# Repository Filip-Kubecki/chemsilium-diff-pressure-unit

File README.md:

# Pressure Measurement Unit - Chemsilium

A differential pressure acquisition system developed for the **Chemsilium Science Club**. This project integrates a **BMP280** (for ambient barometric pressure as calibration point) and dual *MPXM2202GS/AS* setup for differential pressure measurement.

## Repository Structure

The project is organized into four main branches to ensure maintainability:

* **`/hardware`**: Contains **KiCad** PCB and electronic design files.
  <!-- * `sch/`: Schematic diagrams. -->
  <!-- * `pcb/`: Board layout and routing. -->
  <!-- * `fabrication/`: Production-ready Gerbers, BOM (Bill of Materials), and CPL files. -->
* **`/firmware`**: Source code for the **Arduino/C++** embedded system.
  * Handles I2C communication with sensors.
  * Manages data packet formatting for serial transmission (using UART).
* **`/software`**: Desktop application scripts for data visualization and logging.
  * Real-time graphing of pressure trends.
  * CSV logging for post-experimental analysis.
* **`/docs`**: Technical documentation, including user manual with setup, maintenance and use explanations.

---

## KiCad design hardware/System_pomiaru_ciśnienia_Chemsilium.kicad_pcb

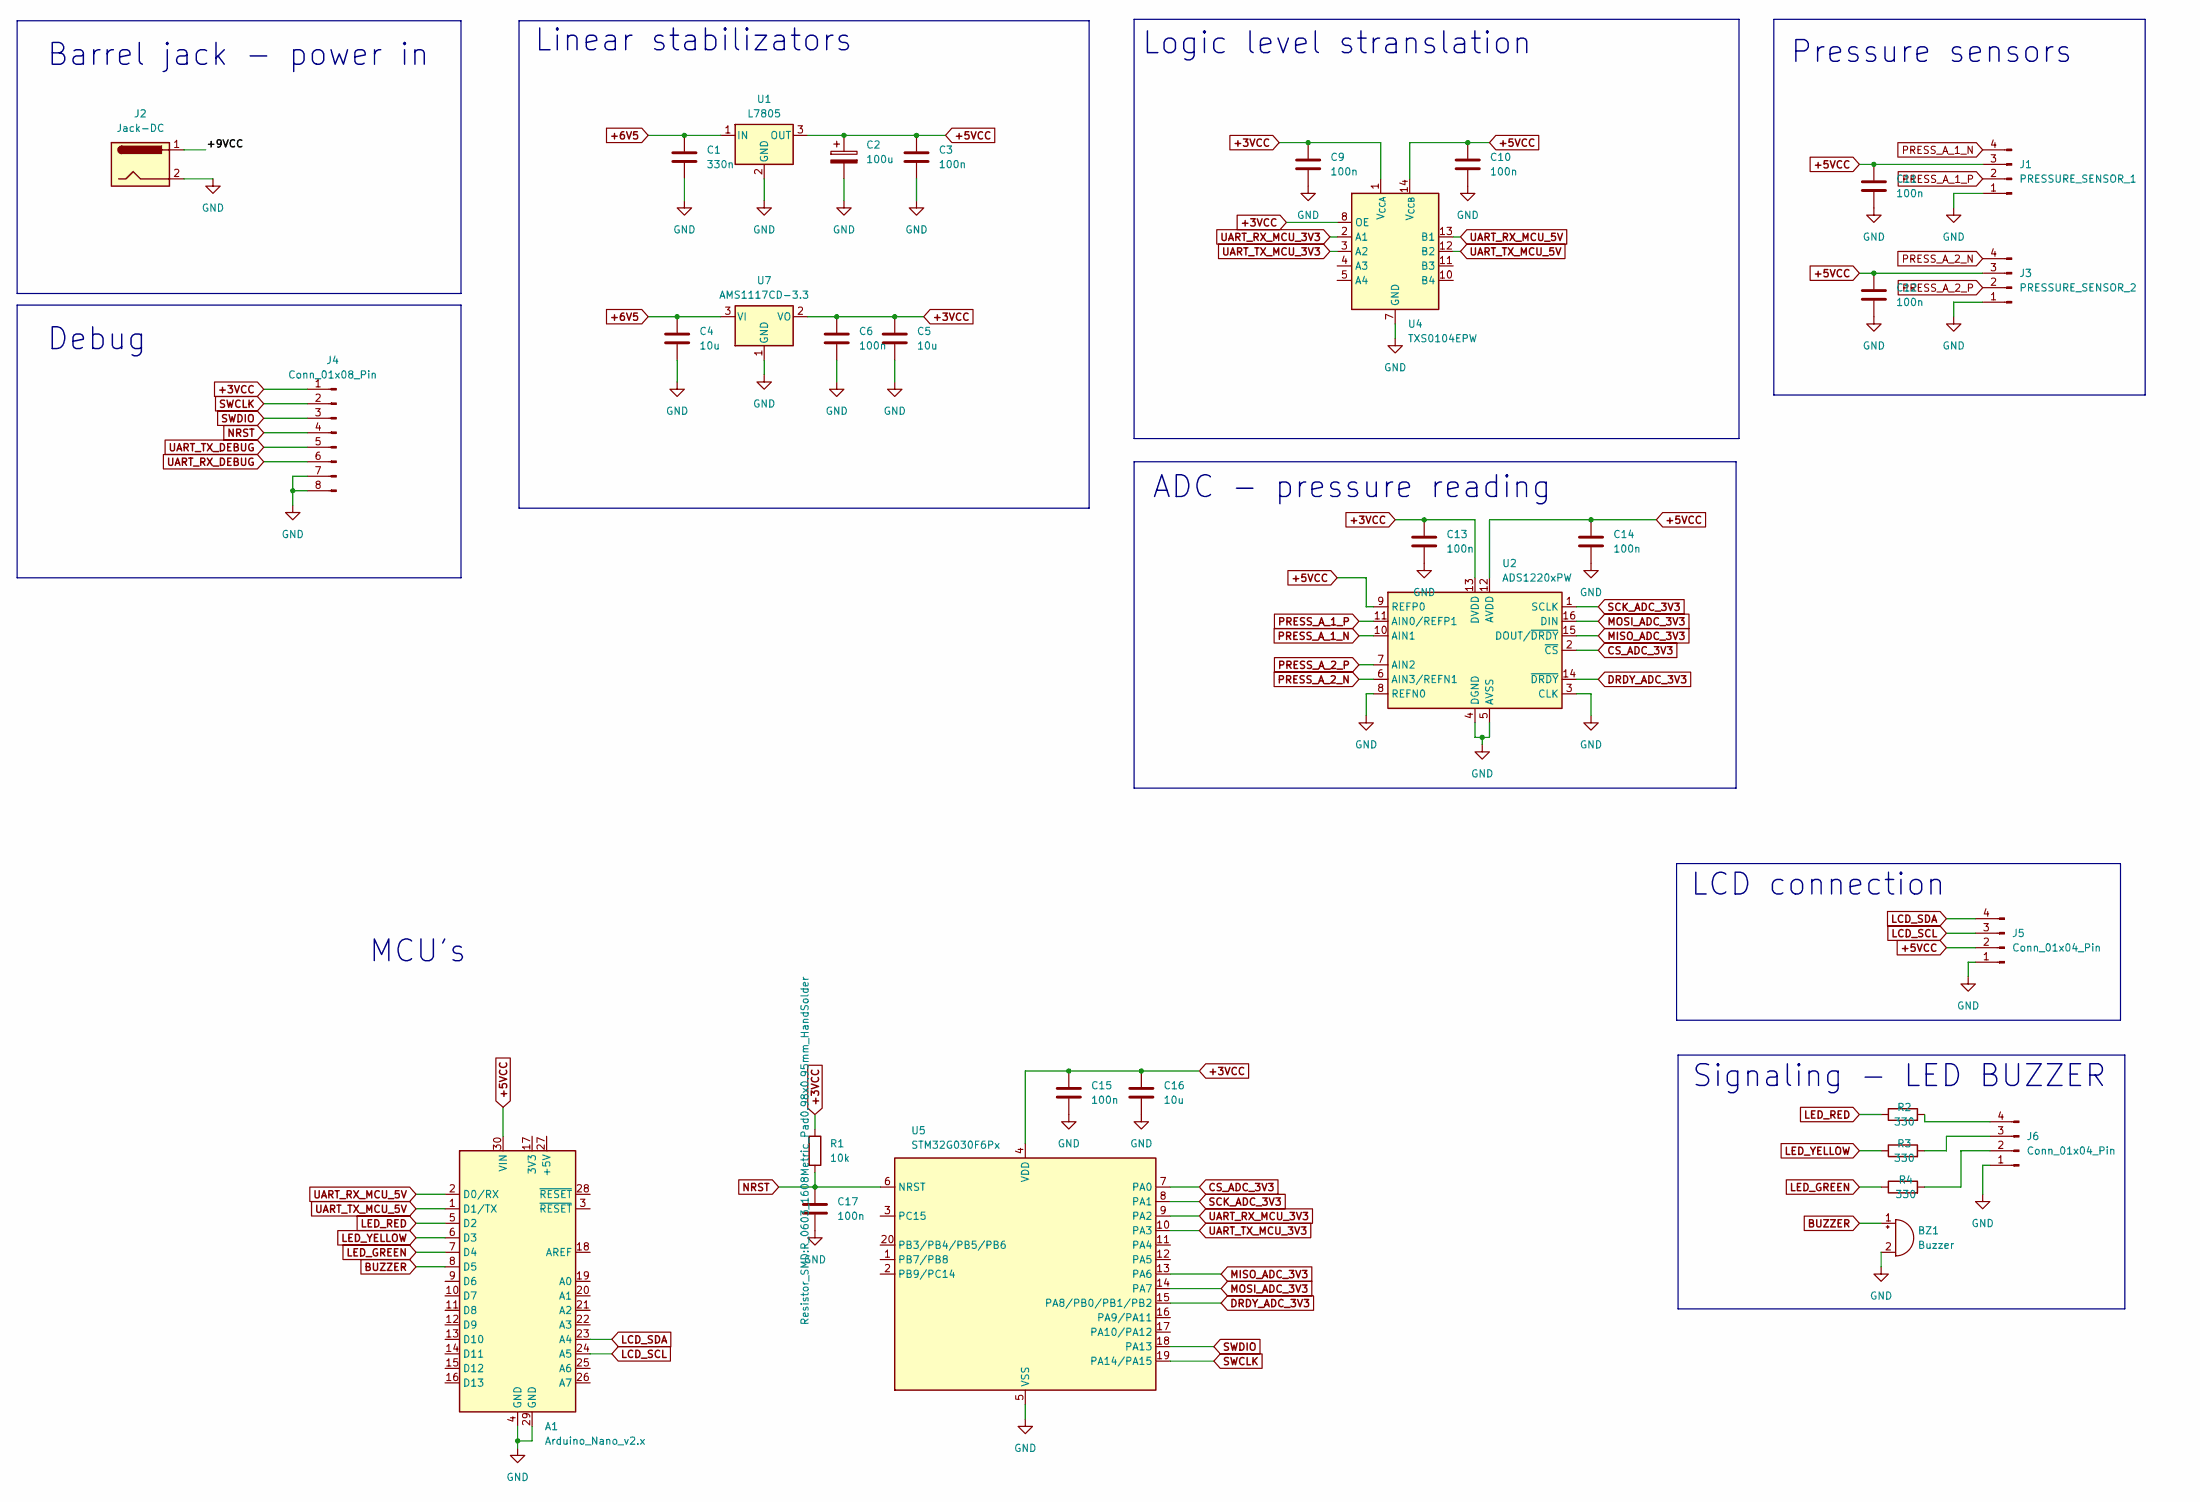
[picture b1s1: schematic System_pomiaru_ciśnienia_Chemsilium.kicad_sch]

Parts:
A1: Arduino_Nano_v2.x; Arduino_Nano
BZ1: Buzzer; Buzzer_12x9.5RM7.6
C1: 330n; CP_Radial_Tantal_D4.5mm_P2.50mm
C2: 100u; CP_Radial_D8.0mm_P3.80mm
C3, C6, C9, C10, C11, C12, C13, C14, C15, C17: 100n; C_0603_1608Metric_Pad1.08x0.95mm_HandSolder
C4, C5, C16: 10u; C_0805_2012Metric_Pad1.18x1.45mm_HandSolder
J1: PRESSURE_SENSOR_1; mpx2202
J2: Jack-DC; BarrelJack_CUI_PJ-102AH_Horizontal
J3: PRESSURE_SENSOR_2; mpx2202
J4: Conn_01x08_Pin; PinHeader_2x04_P2.54mm_Vertical
J5, J6: Conn_01x04_Pin; PinHeader_1x04_P2.54mm_Vertical
R1: 10k; R_0603_1608Metric_Pad0.98x0.95mm_HandSolder
R2, R3, R4: 330; R_Axial_DIN0207_L6.3mm_D2.5mm_P2.54mm_Vertical
U1: L7805; TO-220-3_Vertical
U2: ADS1220xPW; TSSOP-16_4.4x5mm_P0.65mm
U4: TXS0104EPW; TSSOP-14_4.4x5mm_P0.65mm
U5: STM32G030F6Px; TSSOP-20_4.4x6.5mm_P0.65mm
U7: AMS1117CD-3.3; TO-252-3_TabPin2

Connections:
+3VCC: C5.1, C6.1, C9.1, C13.1, C15.1, C16.1, J4.1, R1.1, U2.13 (DVDD), U4.1 (V_{CCA}), U4.8 (OE), U5.4 (VDD), U7.2 (VO)
+5VCC: A1.30 (VIN), C2.1, C3.1, C10.1, C11.1, C12.1, C14.1, J1.3, J3.3, J5.2, U1.3 (OUT), U2.9 (REFP0), U2.12 (AVDD), U4.14 (V_{CCB})
+6V5: C1.1, C4.1, U1.1 (IN), U7.3 (VI)
/+9VCC: J2.1
BUZZER: A1.8 (D5), BZ1.1 (+)
CS_ADC_3V3: U2.2 (~CS), U5.7 (PA0)
DRDY_ADC_3V3: U2.14 (~DRDY), U5.15 (PA8/PB0/PB1/PB2)
GND: A1.4 (GND), A1.29 (GND), BZ1.2 (-), C1.2, C2.2, C3.2, C4.2, C5.2, C6.2, C9.2, C10.2, C11.2, C12.2, C13.2, C14.2, C15.2, C16.2, C17.2, J1.1, J2.2, J3.1, J4.7, J4.8, J5.1, J6.1, U1.2 (GND), U2.3 (CLK), U2.4 (DGND), U2.5 (AVSS), U2.8 (REFN0), U4.7 (GND), U5.5 (VSS), U7.1 (GND)
LCD_SCL: A1.24 (A5), J5.3
LCD_SDA: A1.23 (A4), J5.4
LED_GREEN: A1.7 (D4), R4.1
LED_RED: A1.5 (D2), R2.1
LED_YELLOW: A1.6 (D3), R3.1
MISO_ADC_3V3: U2.15 (DOUT/~DRDY), U5.13 (PA6)
MOSI_ADC_3V3: U2.16 (DIN), U5.14 (PA7)
NRST: C17.1, J4.4, R1.2, U5.6 (NRST)
unnamed: J6.2, R4.2
unnamed: J6.3, R3.2
unnamed: J6.4, R2.2
PRESS_A_1_N: J1.4, U2.10 (AIN1)
PRESS_A_1_P: J1.2, U2.11 (AIN0/REFP1)
PRESS_A_2_N: J3.4, U2.6 (AIN3/REFN1)
PRESS_A_2_P: J3.2, U2.7 (AIN2)
SCK_ADC_3V3: U2.1 (SCLK), U5.8 (PA1)
SWCLK: J4.2, U5.19 (PA14/PA15)
SWDIO: J4.3, U5.18 (PA13)
UART_RX_DEBUG: J4.6
UART_RX_MCU_3V3: U4.2 (A1), U5.9 (PA2)
UART_RX_MCU_5V: A1.2 (D0/RX), U4.13 (B1)
UART_TX_DEBUG: J4.5
UART_TX_MCU_3V3: U4.3 (A2), U5.10 (PA3)
UART_TX_MCU_5V: A1.1 (D1/TX), U4.12 (B2)

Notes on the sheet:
Linear stabilizators
LCD connection
Pressure sensors
Debug
MCU's
ADC - pressure reading
Barrel jack - power in
Signaling - LED BUZZER
Logic level stranslation

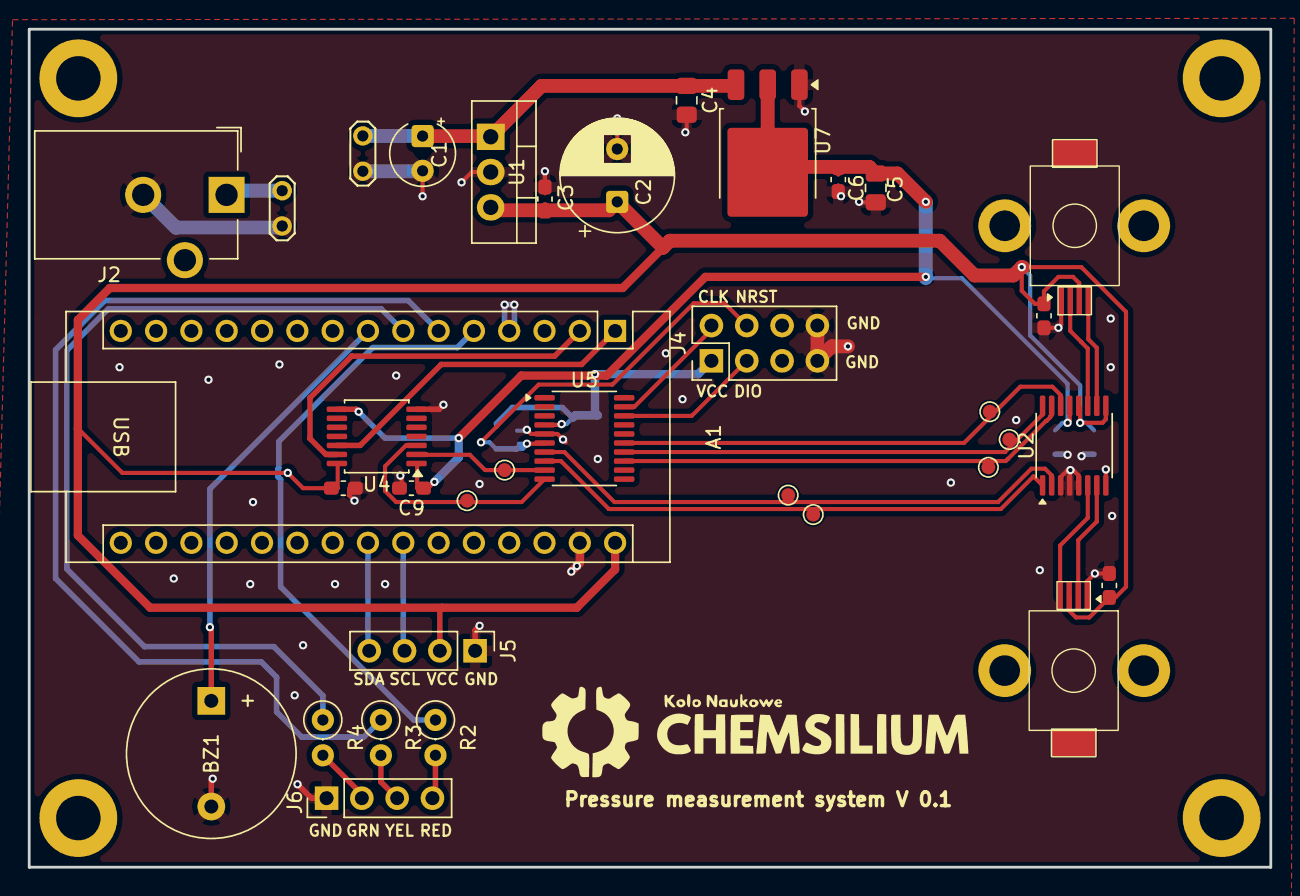
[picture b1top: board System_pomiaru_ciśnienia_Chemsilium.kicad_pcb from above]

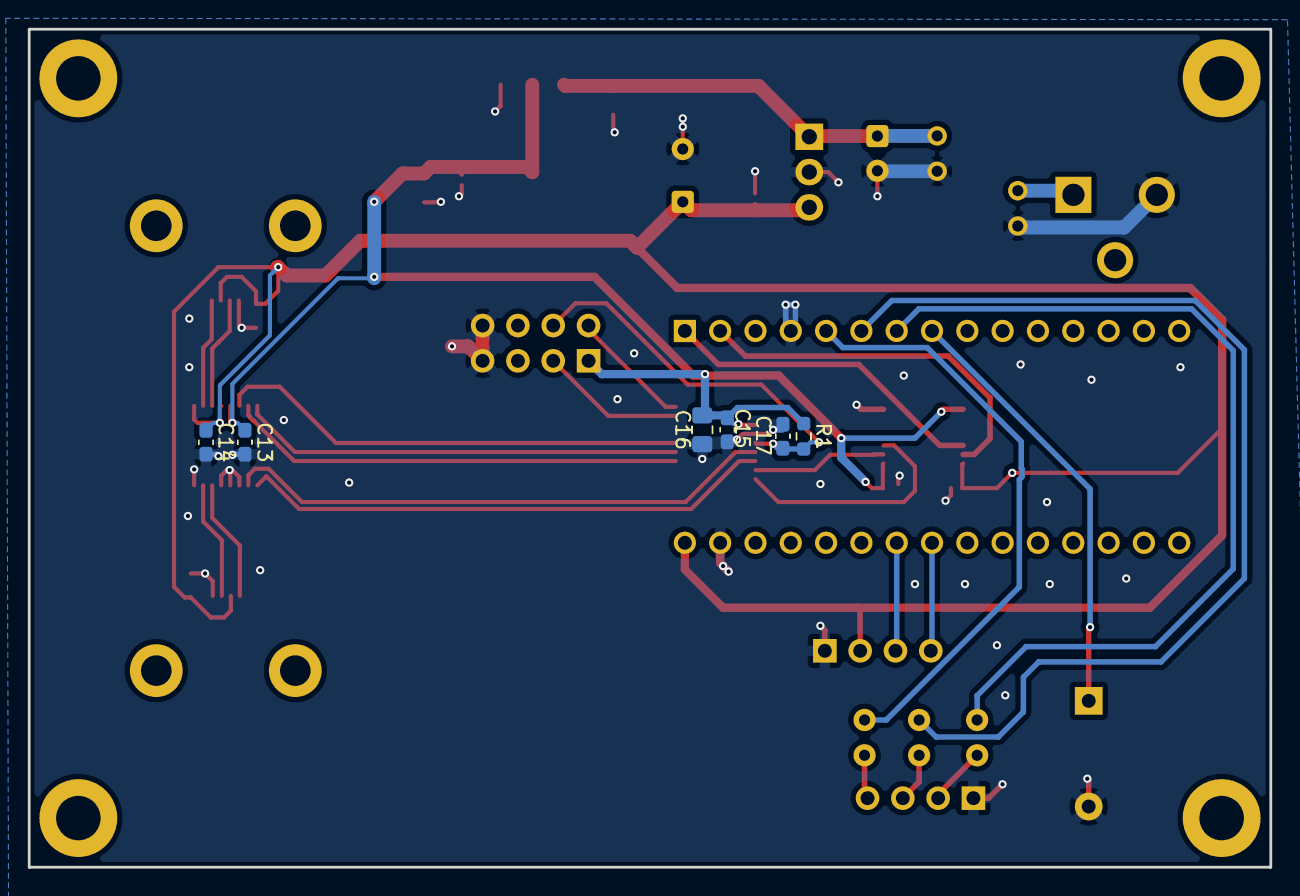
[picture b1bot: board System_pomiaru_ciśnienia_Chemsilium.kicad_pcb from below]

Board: 2 copper layers, 89.3 x 60.3 mm, 32 parts (6 on the bottom side), 29 nets.

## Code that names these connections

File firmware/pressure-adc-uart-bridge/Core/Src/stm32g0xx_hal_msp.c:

/* USER CODE BEGIN Header */
/**
  ******************************************************************************
  * @file         stm32g0xx_hal_msp.c
  * @brief        This file provides code for the MSP Initialization
  *               and de-Initialization codes.
  ******************************************************************************
  * @attention
  *
  * Copyright (c) 2026 STMicroelectronics.
  * All rights reserved.
  *
  * This software is licensed under terms that can be found in the LICENSE file
  * in the root directory of this software component.
  * If no LICENSE file comes with this software, it is provided AS-IS.
  *
  ******************************************************************************
  */
/* USER CODE END Header */
/* Includes ------------------------------------------------------------------*/
#include "main.h"
/* USER CODE BEGIN Includes */

/* USER CODE END Includes */

/* Private typedef -----------------------------------------------------------*/
/* USER CODE BEGIN TD */

/* USER CODE END TD */

/* Private define ------------------------------------------------------------*/
/* USER CODE BEGIN Define */

/* USER CODE END Define */

/* Private macro -------------------------------------------------------------*/
/* USER CODE BEGIN Macro */

/* USER CODE END Macro */

/* Private variables ---------------------------------------------------------*/
/* USER CODE BEGIN PV */

/* USER CODE END PV */

/* Private function prototypes -----------------------------------------------*/
/* USER CODE BEGIN PFP */

/* USER CODE END PFP */

/* External functions --------------------------------------------------------*/
/* USER CODE BEGIN ExternalFunctions */

/* USER CODE END ExternalFunctions */

/* USER CODE BEGIN 0 */

/* USER CODE END 0 */
/**
  * Initializes the Global MSP.
  */
void HAL_MspInit(void)
{

  /* USER CODE BEGIN MspInit 0 */

  /* USER CODE END MspInit 0 */

  __HAL_RCC_SYSCFG_CLK_ENABLE();
  __HAL_RCC_PWR_CLK_ENABLE();

  /* System interrupt init*/

  /* USER CODE BEGIN MspInit 1 */

  /* USER CODE END MspInit 1 */
}

/**
  * @brief SPI MSP Initialization
  * This function configures the hardware resources used in this example
  * @param hspi: SPI handle pointer
  * @retval None
  */
void HAL_SPI_MspInit(SPI_HandleTypeDef* hspi)
{
  GPIO_InitTypeDef GPIO_InitStruct = {0};
  if(hspi->Instance==SPI1)
  {
    /* USER CODE BEGIN SPI1_MspInit 0 */

    /* USER CODE END SPI1_MspInit 0 */
    /* Peripheral clock enable */
    __HAL_RCC_SPI1_CLK_ENABLE();

    __HAL_RCC_GPIOA_CLK_ENABLE();
    /**SPI1 GPIO Configuration
    PA1     ------> SPI1_SCK
    PA6     ------> SPI1_MISO
    PA7     ------> SPI1_MOSI
    */
    GPIO_InitStruct.Pin = GPIO_PIN_1|GPIO_PIN_6|GPIO_PIN_7;
    GPIO_InitStruct.Mode = GPIO_MODE_AF_PP;
    GPIO_InitStruct.Pull = GPIO_NOPULL;
    GPIO_InitStruct.Speed = GPIO_SPEED_FREQ_LOW;
    GPIO_InitStruct.Alternate = GPIO_AF0_SPI1;
    HAL_GPIO_Init(GPIOA, &GPIO_InitStruct);

    /* USER CODE BEGIN SPI1_MspInit 1 */

    /* USER CODE END SPI1_MspInit 1 */

  }

}

/**
  * @brief SPI MSP De-Initialization
  * This function freeze the hardware resources used in this example
  * @param hspi: SPI handle pointer
  * @retval None
  */
void HAL_SPI_MspDeInit(SPI_HandleTypeDef* hspi)
{
  if(hspi->Instance==SPI1)
  {
    /* USER CODE BEGIN SPI1_MspDeInit 0 */

    /* USER CODE END SPI1_MspDeInit 0 */
    /* Peripheral clock disable */
    __HAL_RCC_SPI1_CLK_DISABLE();

    /**SPI1 GPIO Configuration
    PA1     ------> SPI1_SCK
    PA6     ------> SPI1_MISO
    PA7     ------> SPI1_MOSI
    */
    HAL_GPIO_DeInit(GPIOA, GPIO_PIN_1|GPIO_PIN_6|GPIO_PIN_7);

    /* USER CODE BEGIN SPI1_MspDeInit 1 */

    /* USER CODE END SPI1_MspDeInit 1 */
  }

}

/**
  * @brief UART MSP Initialization
  * This function configures the hardware resources used in this example
  * @param huart: UART handle pointer
  * @retval None
  */
void HAL_UART_MspInit(UART_HandleTypeDef* huart)
{
  GPIO_InitTypeDef GPIO_InitStruct = {0};
  if(huart->Instance==USART2)
  {
    /* USER CODE BEGIN USART2_MspInit 0 */

    /* USER CODE END USART2_MspInit 0 */
    /* Peripheral clock enable */
    __HAL_RCC_USART2_CLK_ENABLE();

    __HAL_RCC_GPIOA_CLK_ENABLE();
    /**USART2 GPIO Configuration
    PA2     ------> USART2_TX
    PA3     ------> USART2_RX
    */
    GPIO_InitStruct.Pin = GPIO_PIN_2|GPIO_PIN_3;
    GPIO_InitStruct.Mode = GPIO_MODE_AF_PP;
    GPIO_InitStruct.Pull = GPIO_NOPULL;
    GPIO_InitStruct.Speed = GPIO_SPEED_FREQ_LOW;
    GPIO_InitStruct.Alternate = GPIO_AF1_USART2;
    HAL_GPIO_Init(GPIOA, &GPIO_InitStruct);

    /* USER CODE BEGIN USART2_MspInit 1 */

    /* USER CODE END USART2_MspInit 1 */

  }

}

/**
  * @brief UART MSP De-Initialization
  * This function freeze the hardware resources used in this example
  * @param huart: UART handle pointer
  * @retval None
  */
void HAL_UART_MspDeInit(UART_HandleTypeDef* huart)
{
  if(huart->Instance==USART2)
  {
    /* USER CODE BEGIN USART2_MspDeInit 0 */

    /* USER CODE END USART2_MspDeInit 0 */
    /* Peripheral clock disable */
    __HAL_RCC_USART2_CLK_DISABLE();

    /**USART2 GPIO Configuration
    PA2     ------> USART2_TX
    PA3     ------> USART2_RX
    */
    HAL_GPIO_DeInit(GPIOA, GPIO_PIN_2|GPIO_PIN_3);

    /* USER CODE BEGIN USART2_MspDeInit 1 */

    /* USER CODE END USART2_MspDeInit 1 */
  }

}

/* USER CODE BEGIN 1 */

/* USER CODE END 1 */

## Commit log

2026-04-02 [POC] Basic measurement for MX2202 with "calibration"
    Backup of old files used for fast check of MXP2202 sensor.
2026-04-02 [POC] Backup of test PCB for MPX2202 developement
    This PCB is prototype used for ease of testing MPX2202 sensors. Board
    already has differential path for analog outputs and ADS1X015 mounted on
    it. It is easy to etch in home design.
2026-06-21 [feat] Initial test design for differential pressure sensor PCB
    Initial PCB prototype for differential pressure measurement device.
    Identified issues for future iterations:
    - UART conflict between STM32 and Arduino Nano.
    - Incorrect footprint for MPXM2202 sensor (pitch too small).
    - Missing dedicated header for BMP280.
    - Insufficient expansion pins (GPIOs for encoder).
2026-06-22 [feat] Add STM32-to-Arduino data bridge and ADS1220 driver
    Implemented complete firmware for STM32G030F6 to interface with two
    pressure sensors via ADS1220 ADC. Features include SPI communication for
    sensor data acquisition and UART transmission to forward processed
    pressure values to an Arduino Nano.
2026-06-24 [feat] Improved data transmission for STM32
